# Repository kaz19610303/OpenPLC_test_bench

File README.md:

# OpenPLC Test Bench Board

Testing OpenPLC

For Arduino UNO  
For Spresense + Extension board

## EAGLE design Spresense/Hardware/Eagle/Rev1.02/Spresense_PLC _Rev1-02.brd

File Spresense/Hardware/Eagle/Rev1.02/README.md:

###Test bench board for Spresense  
Rev 1.02

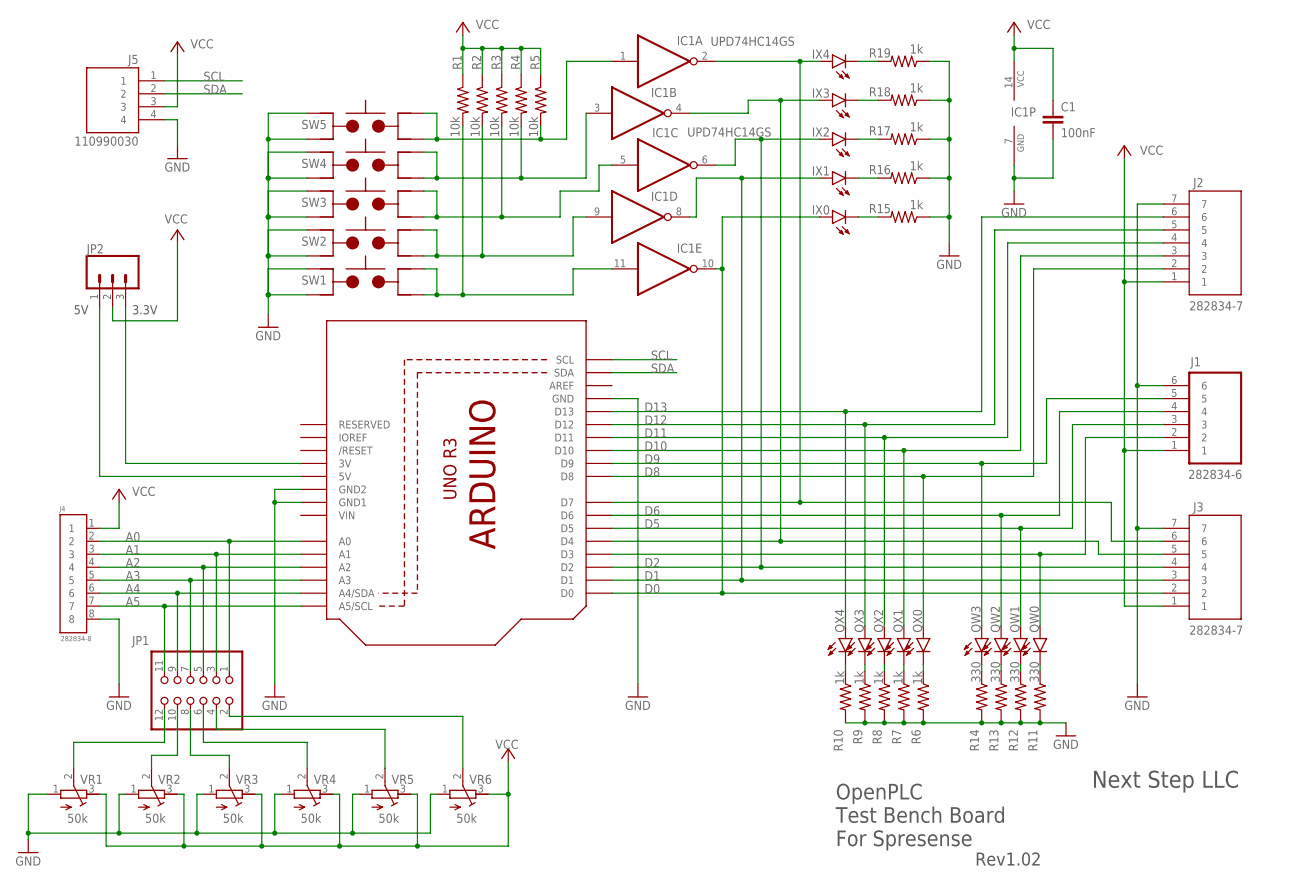
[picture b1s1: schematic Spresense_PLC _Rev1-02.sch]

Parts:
C1: 100nF; C0603
IC1: UPD74HC14GS; SO14
IX0, IX1, IX2, IX3, IX4: LEDCHIP-LED0603; CHIP-LED0603
J1: 282834-6; TE_282834-6
J2, J3: 282834-7; TE_282834-7
J4: 282834-8; HDRV8W85P254_8X1_2078X650X1000
J5: 110990030; SEEED_110990030
JP1: PINHD-2X6; 2X06
JP2: 455-1750-1-ND; 1X03
QW0, QW1, QW2, QW3: LEDCHIP-LED0603; CHIP-LED0603
QX0, QX1, QX2, QX3, QX4: LEDCHIP-LED0603; CHIP-LED0603
R1, R2, R3, R4, R5: 10k; R0603
R6, R7, R8, R9, R10, R15, R16, R17, R18, R19: 1k; R0603
R11, R12, R13, R14: 330; R0603
SW1, SW2, SW3, SW4, SW5: TL3342F160QG/TR; SW_TL3342F160QG/TR
U1: ARDUINOR3-DIMENSION; ARDUINOR3
VR1, VR2, VR3, VR4, VR5, VR6: 50k; RTRIM3339P

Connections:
A0: J4.2, JP1.1, U1.A0
A1: J4.3, JP1.3, U1.A1
A2: J4.4, JP1.5, U1.A2
A3: J4.5, JP1.7, U1.A3
A4: J4.6, JP1.9, U1.A4 (A4/SDA)
A5: J4.7, JP1.11, U1.A5 (A5/SCL)
D0: IC1.10 (O), IX0.A, J3.2, U1.D0
D1: IC1.8 (O), IX1.A, J3.3, U1.D1
D2: IC1.6 (O), IX2.A, J3.4, U1.D2
D5: IC1.4 (O), IX3.A, J3.5, U1.D4
D6: IC1.2 (O), IX4.A, J3.6, U1.D7
D8: J2.2, QX0.A, U1.D8
D9: J1.5, QW3.A, U1.D9
D10: J2.3, QX1.A, U1.D10
D11: J2.4, QX2.A, U1.D11
D12: J2.5, QX3.A, U1.D12
D13: J2.6, QX4.A, U1.D13
GND: C1.2, IC1.7 (GND), J1.6, J2.7, J3.7, J4.8, J5.4, R6.2, R7.2, R8.2, R9.2, R10.2, R11.2, R12.2, R13.2, R14.2, R15.1, R16.1, R17.1, R18.1, R19.1, SW1.3, SW1.4, SW2.3, SW2.4, SW3.3, SW3.4, SW4.3, SW4.4, SW5.3, SW5.4, U1.GND, U1.GND1, U1.GND2, VR1.1 (A), VR2.1 (A), VR3.1 (A), VR4.1 (A), VR5.1 (A), VR6.1 (A)
unnamed: QX3.C, R9.1
unnamed: QX2.C, R8.1
unnamed: QX1.C, R7.1
unnamed: QX0.C, R6.1
unnamed: QW2.C, R13.1
unnamed: QW1.C, R12.1
unnamed: QW0.C, R11.1
unnamed: JP1.12, VR1.2 (S)
unnamed: JP1.10, VR2.2 (S)
unnamed: JP1.8, VR3.2 (S)
unnamed: JP1.6, VR4.2 (S)
unnamed: JP1.4, VR5.2 (S)
unnamed: JP1.2, VR6.2 (S)
unnamed: JP2.3, U1.3V
unnamed: J1.2, QW0.A, U1.D3
unnamed: JP2.1, U1.5V
unnamed: IX4.C, R19.2
unnamed: IX3.C, R18.2
unnamed: IX2.C, R17.2
unnamed: IX1.C, R16.2
unnamed: IX0.C, R15.2
unnamed: J1.3, QW1.A, U1.D5
unnamed: J1.4, QW2.A, U1.D6
unnamed: QW3.C, R14.1
unnamed: QX4.C, R10.1
unnamed: IC1.11 (I), R1.2, SW1.1, SW1.2
unnamed: IC1.9 (I), R2.2, SW2.1, SW2.2
unnamed: IC1.5 (I), R3.2, SW3.1, SW3.2
unnamed: IC1.3 (I), R4.2, SW4.1, SW4.2
unnamed: IC1.1 (I), R5.2, SW5.1, SW5.2
SCL: J5.1, U1.SCL
SDA: J5.2, U1.SDA
VCC: C1.1, IC1.14 (VCC), J1.1, J2.1, J3.1, J4.1, J5.3, JP2.2, R1.1, R2.1, R3.1, R4.1, R5.1, VR1.3 (E), VR2.3 (E), VR3.3 (E), VR4.3 (E), VR5.3 (E), VR6.3 (E)
VIN: U1.VIN

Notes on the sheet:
OpenPLC Test Bench Board For Spresense
Rev1.02
Next Step LLC
3.3V

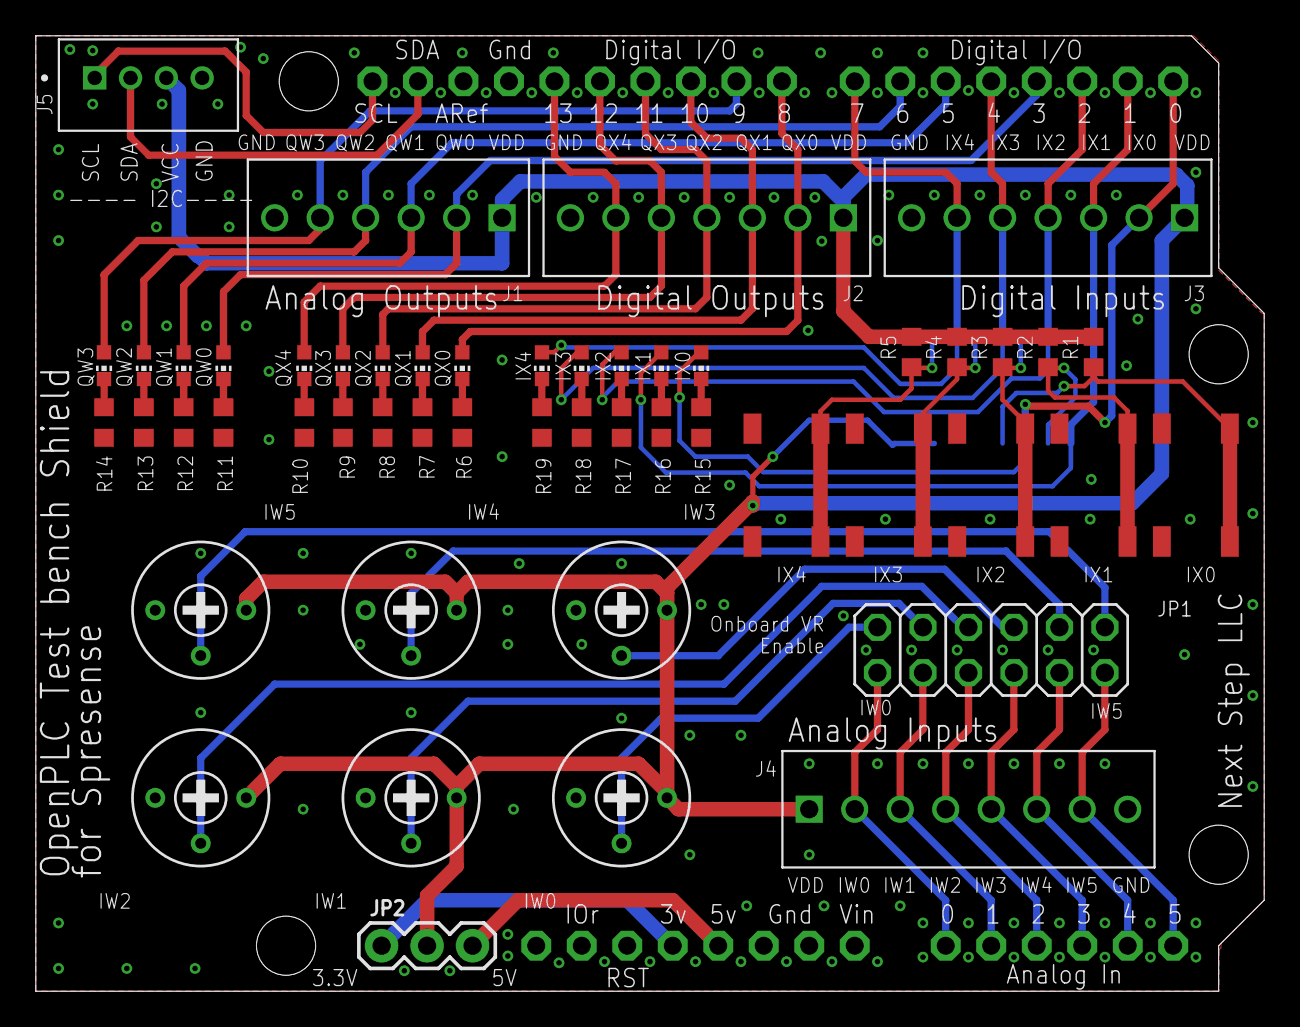
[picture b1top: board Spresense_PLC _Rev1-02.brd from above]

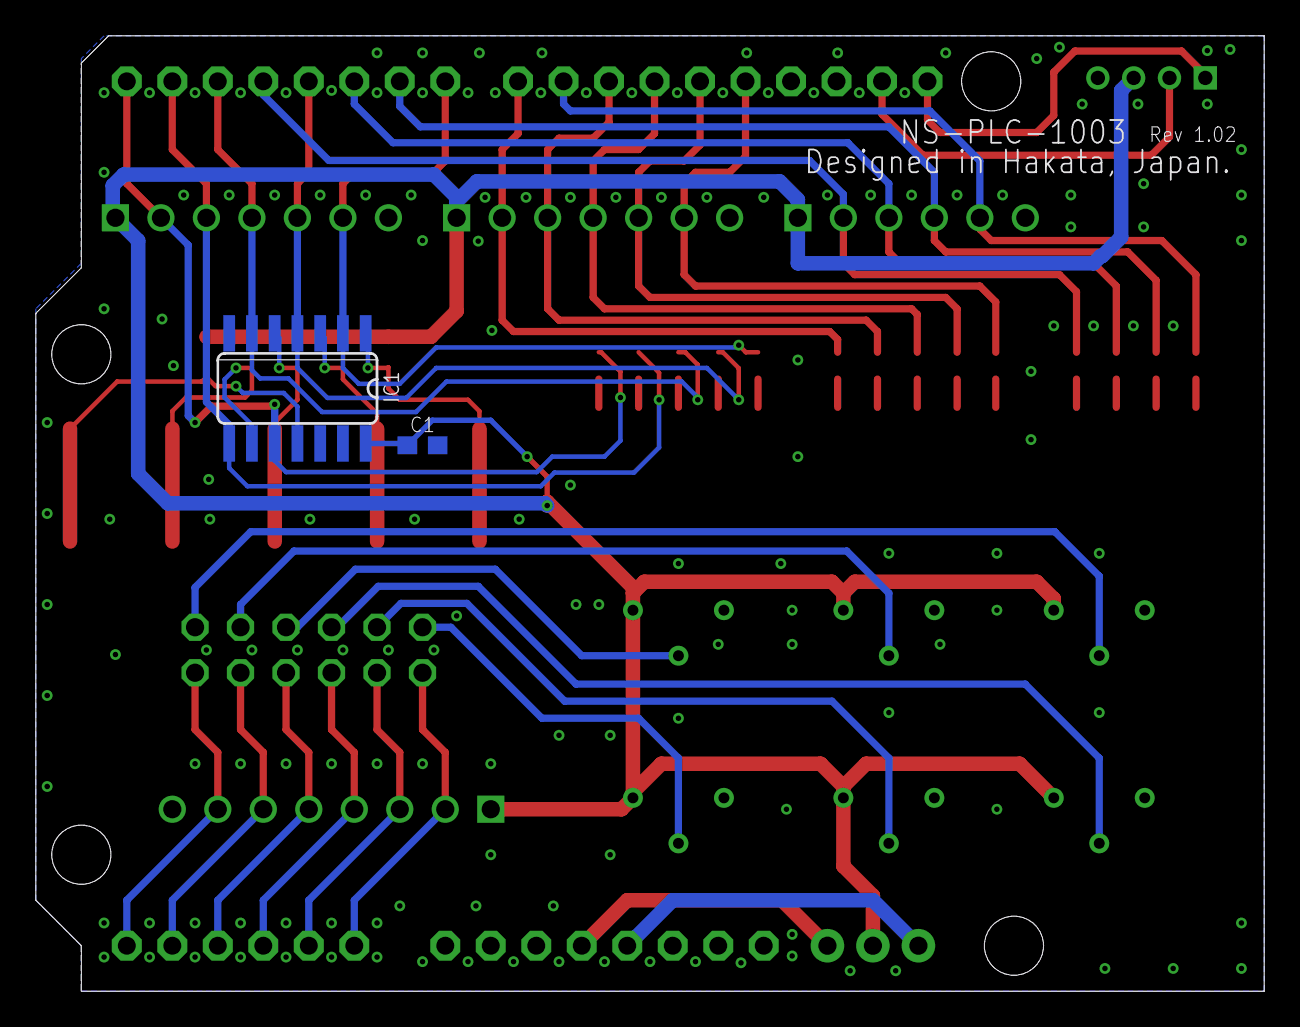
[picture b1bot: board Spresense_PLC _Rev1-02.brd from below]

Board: 2 copper layers, 68.6 x 53.3 mm, 54 parts (2 on the bottom side), 51 nets.

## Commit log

2023-01-12 First commit.
2023-01-12 Gerber file upload.
2023-01-12 Gerver file upload
2023-01-12 Gerver file upload.
2023-01-13 Add Spresense
2023-01-13 Rename READNE.md to README.md
2023-01-13 Spresense Eagle data up.
2023-01-14 部品表更新
2023-01-16 Bench Shield Ladder Program upload.
2023-01-16 Create OpenPLC_LD
2023-02-05 Rename file name
2023-02-05 Hardware Rev1.02

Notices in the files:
parts and their libraries:
SparkFun-Connectors: Licensing: Creative Commons ShareAlike 4.0 International - https://creativecommons.org/licenses/by-sa/4.0
